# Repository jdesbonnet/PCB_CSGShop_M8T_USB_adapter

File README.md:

# PCB_CSGShop_M8T_USB_adapter

USB adapter for [pin version of uBlox Neo-M8T](https://www.csgshop.com/product.php?id_product=240) available from CSGShop.

The pin header on the receiver breaks out USB D-/D+, 5V and GND. These can be routed directly to a USB mini or mico connector. For ease of construction I'm using a USB micro breakout board instead of soldering a USB micro connector directly on the board.

There are also headers for other pins including UART TX,RX (J4) and interrupt and timing pulse pins (J3).

## Version 1.0.1, 4 Jan 2019

* Fix missing trace to GND on M8T side of board. Easily patched on V1.0.0 board using a short bodge wire connection to neighboring J3 GND.
* Add extra info to silkscreen

## Version 1.0.0, Dec 2018

* First version.

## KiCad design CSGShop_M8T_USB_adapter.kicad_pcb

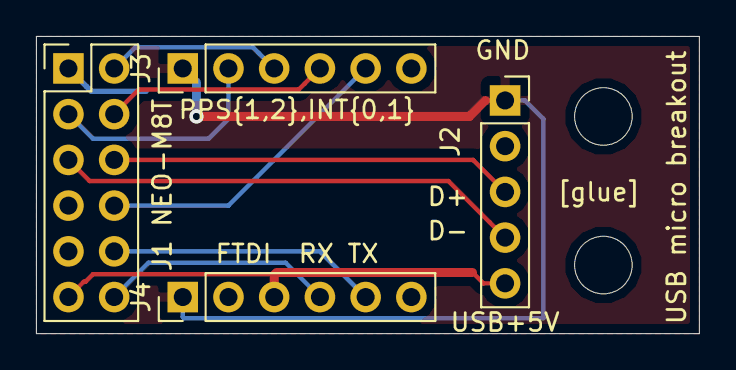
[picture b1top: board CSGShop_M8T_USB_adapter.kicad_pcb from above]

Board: 2 copper layers, 36.8 x 16.5 mm, 4 parts (0 on the bottom side), 10 nets.

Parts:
J1 NEO-M8T: Conn_02x06_Odd_Even; PinHeader_2x06_P2.54mm_Vertical
J2: Conn_01x05; PinSocket_1x05_P2.54mm_Vertical
J3, J4: Conn_01x06_Male; PinHeader_1x06_P2.54mm_Vertical

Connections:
EXTINT0: J1 NEO-M8T.4, J3.4
EXTINT1: J1 NEO-M8T.8, J3.5
GND: J1 NEO-M8T.1, J2.1, J3.1, J4.1
PPS1: J1 NEO-M8T.3, J3.2
PPS2: J1 NEO-M8T.2, J3.3
RX: J1 NEO-M8T.12, J4.4
TX: J1 NEO-M8T.10, J4.5
USB+5V: J1 NEO-M8T.11, J2.5, J4.3
USB_DN: J1 NEO-M8T.5, J2.4
USB_DP: J1 NEO-M8T.6, J2.3

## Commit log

2018-12-10 PCB images
2019-01-05 version 1.0.0 (10 Dec 2018)
2019-01-05 fix missing trace to GND on M8T header
2019-01-05 add extra info on silk screen
